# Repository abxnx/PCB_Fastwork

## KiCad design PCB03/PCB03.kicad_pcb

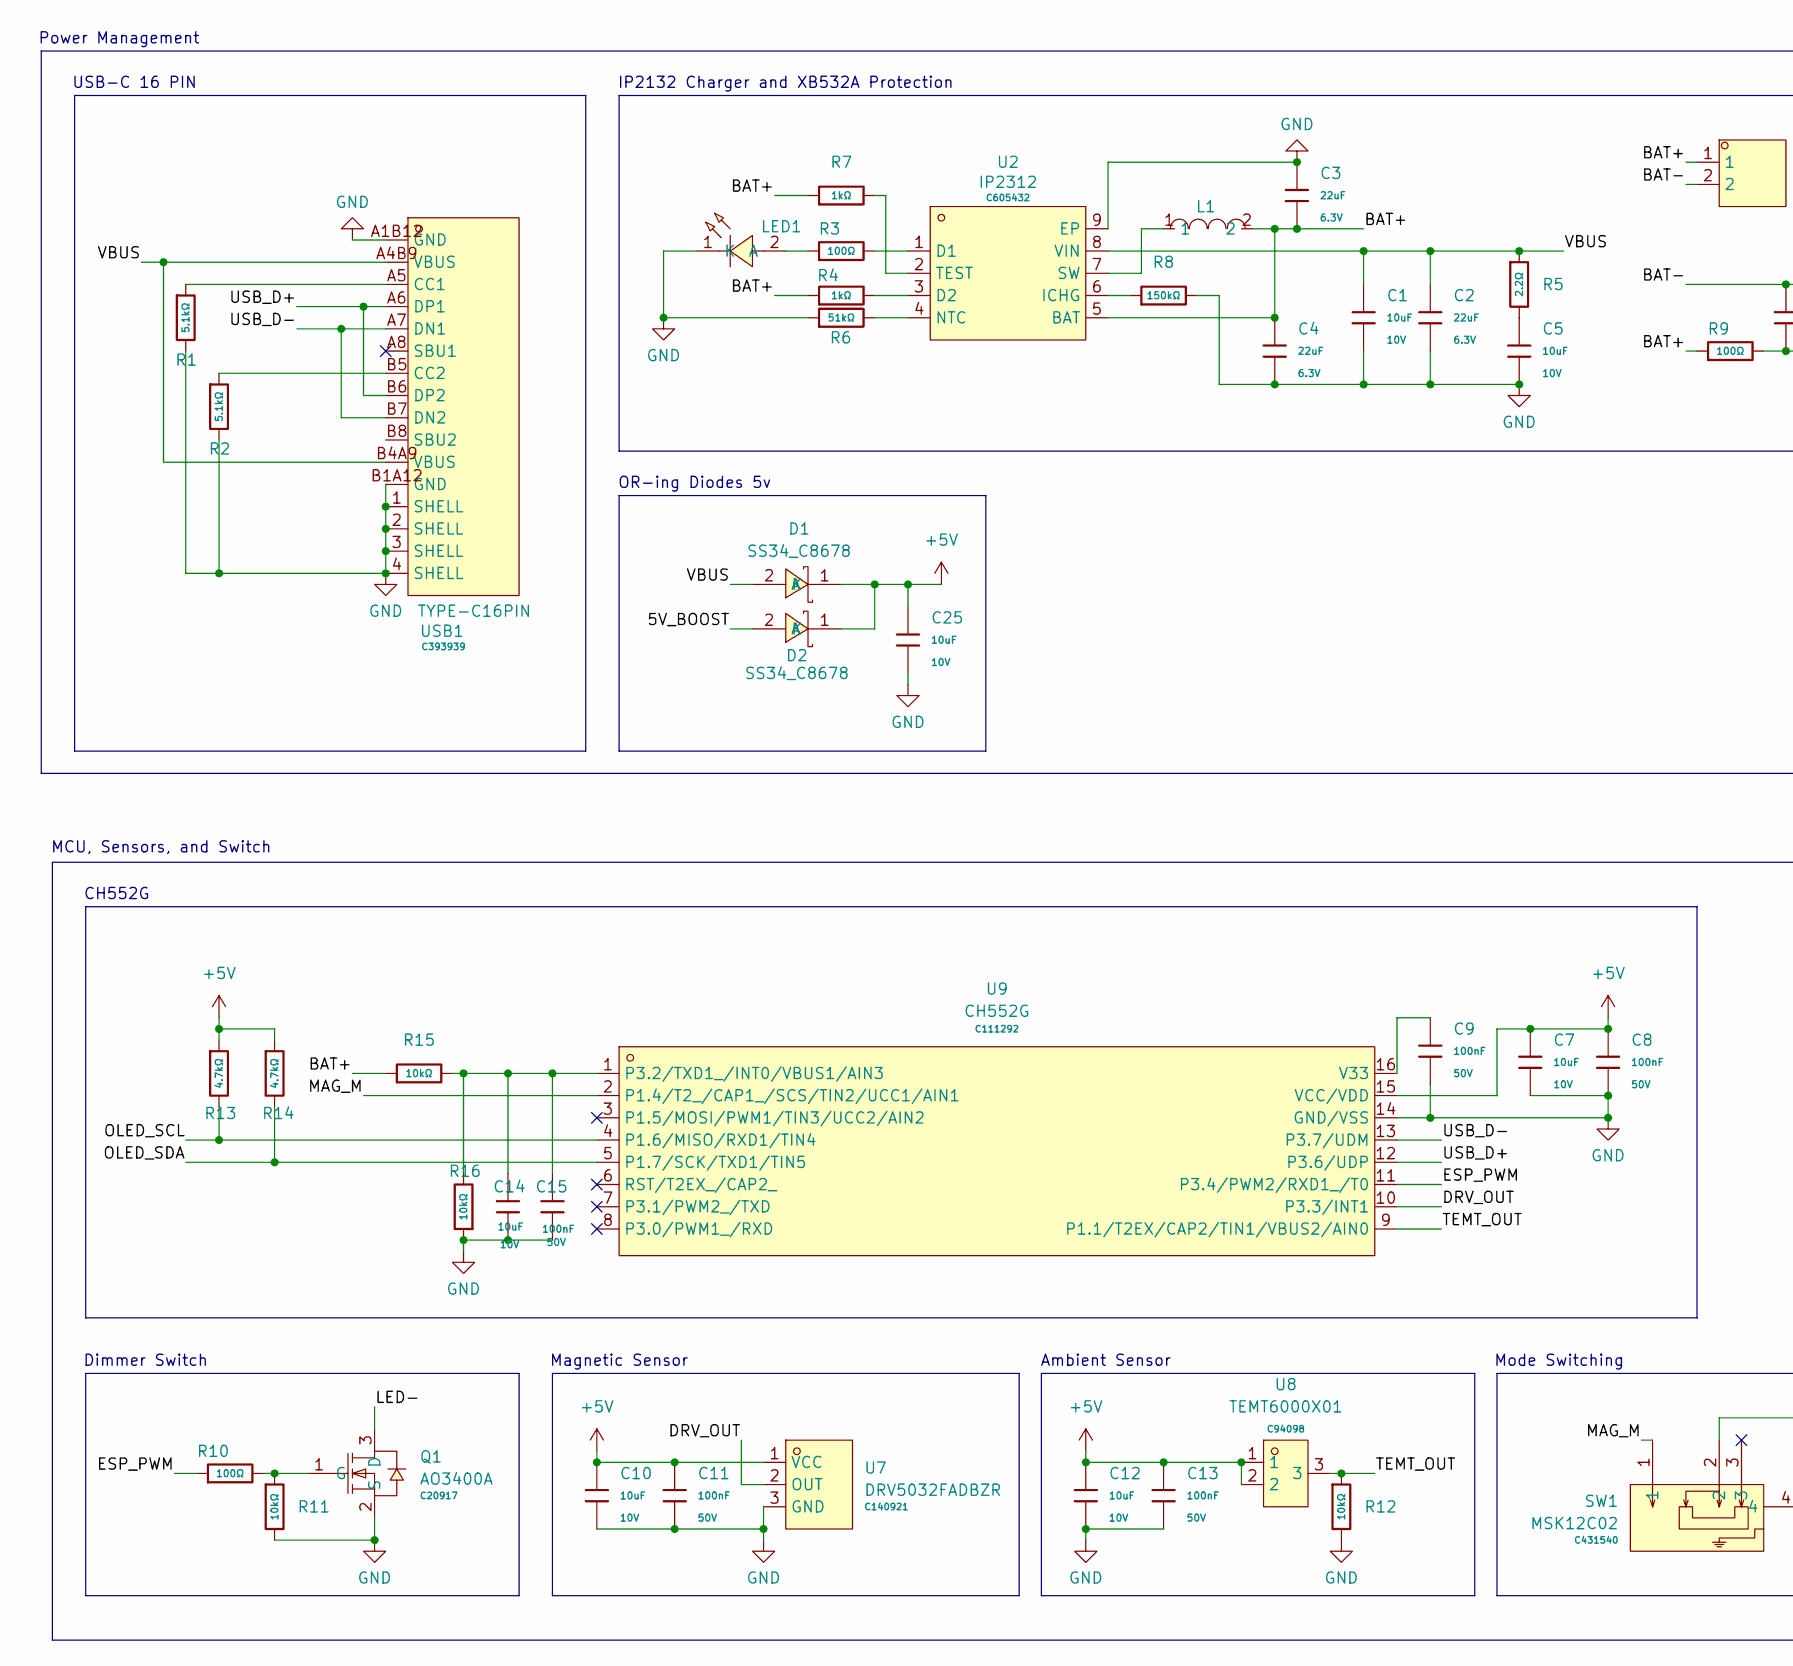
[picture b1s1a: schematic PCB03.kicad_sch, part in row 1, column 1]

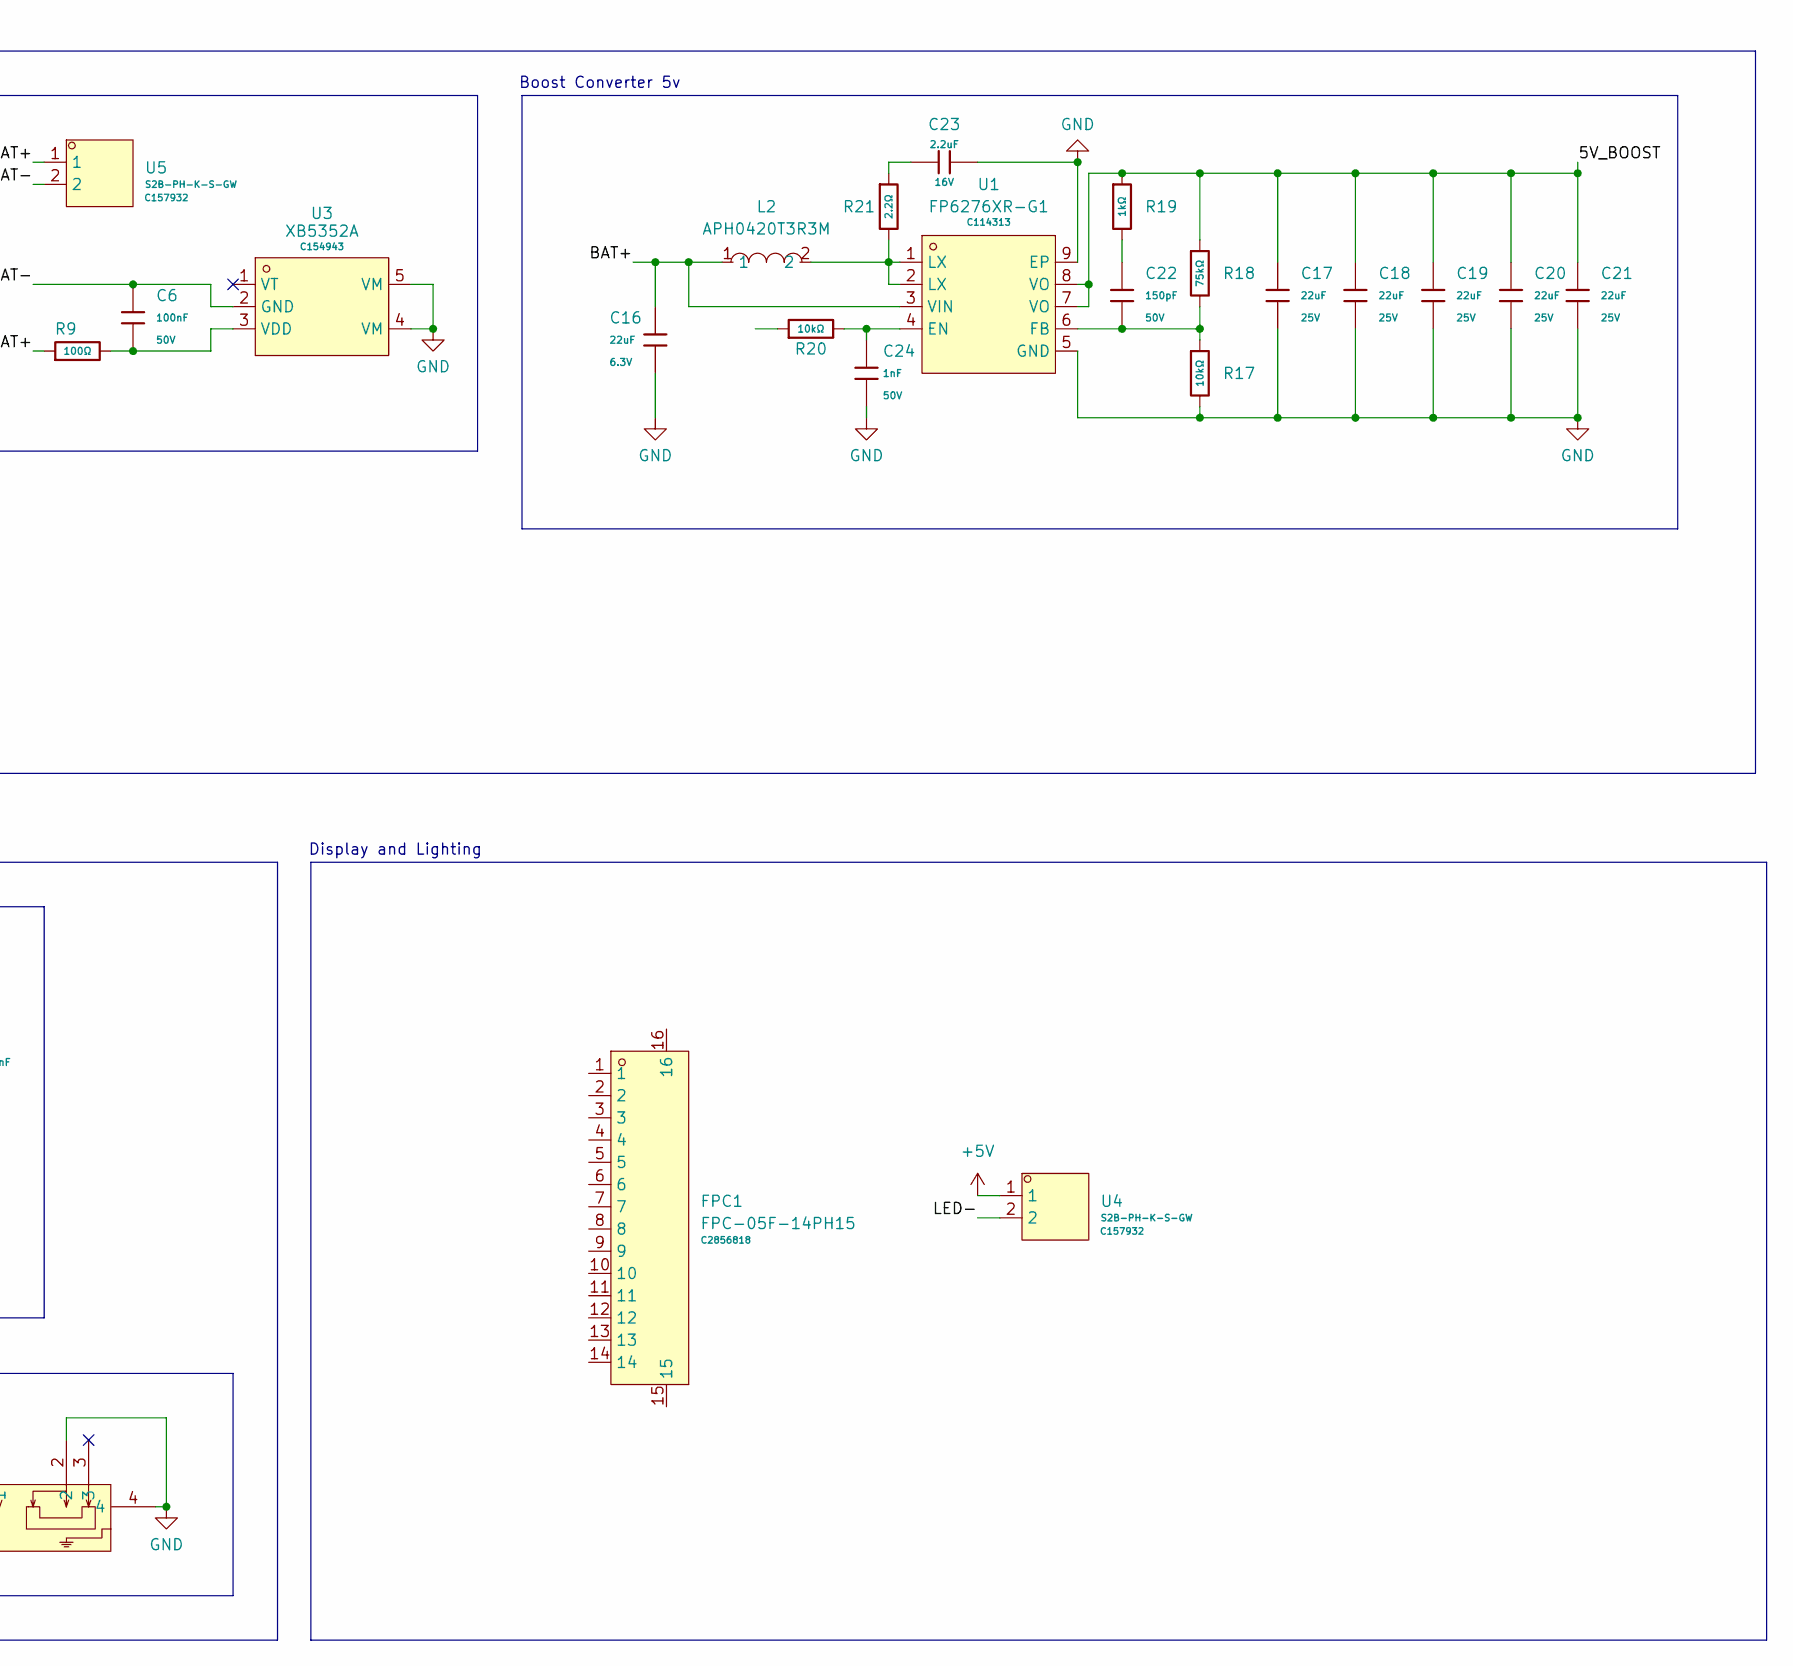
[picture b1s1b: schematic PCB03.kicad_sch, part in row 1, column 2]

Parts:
C1, C5, C7, C10, C12, C14, C25: 10uF; C_0603; Voltage Rated 10V; Tolerance ±10%; Part CL10A106KP8NNNC; LCSC C19702
C2, C3, C4, C16: 22uF; C_0603; Voltage Rated 6.3V; Tolerance ±20%; Part CL10A226MQ8NRNC; LCSC C59461
C6, C8, C9, C11, C13, C15: 100nF; C_0603; Voltage Rated 50V; Tolerance ±10%; Part CC0603KRX7R9BB104; LCSC C14663
C17, C18, C19, C20, C21: 22uF; C_0805; Voltage Rated 25V; Tolerance ±20%; Part CL21A226MAQNNNE; LCSC C45783
C22: 150pF; C_0603; Voltage Rated 50V; Tolerance ±10%; Part 0603B151K500NT; LCSC C1594
C23: 2.2uF; C_0603; Voltage Rated 16V; Tolerance ±10%; Part CL10A225KO8NNNC; LCSC C23630
C24: 1nF; C_0603; Voltage Rated 50V; Tolerance ±10%; Part CL10B102KB8NNNC; LCSC C1588
D1, D2: SS34_C8678; SMA_L4.3-W2.6-LS5.2-RD; MPN SS34; LCSC Part C8678
FPC1: FPC-05F-14PH15; FPC-SMD_14P-P0.50_XUNPU_FPC-05F-14PH15; MPN FPC-05F-14PH15; LCSC Part C2856818
L1: DFE252012F-1R0M=P2; L2520; MPN DFE252012F-1R0M=P2; LCSC Part C435392
L2: APH0420T3R3M; IND-SMD_L4.4-W4.2; MPN APH0420T3R3M; LCSC Part C5349667
LED1: XL-1608SURC-06; LED0603-RD_RED; MPN XL-1608SURC-06; LCSC Part C965799
Q1: AO3400A; SOT-23-3_L2.9-W1.3-P1.90-LS2.4-BR; MPN AO3400A; LCSC Part C20917
R1, R2: 5.1kΩ; R_0603; Overload Voltage (Max) 75V; Tolerance ±1%; Part 0603WAF5101T5E; LCSC C23186
R3, R9, R10: 100Ω; R_0603; Overload Voltage (Max) 75V; Tolerance ±1%; Part 0603WAF1000T5E; LCSC C22775
R4, R7, R19: 1kΩ; R_0603; Overload Voltage (Max) 75V; Tolerance ±1%; Part 0603WAF1001T5E; LCSC C21190
R5, R21: 2.2Ω; R_0603; Overload Voltage (Max) 75V; Tolerance ±1%; Part 0603WAF220KT5E; LCSC C22939
R6: 51kΩ; R_0603; Overload Voltage (Max) 75V; Tolerance ±1%; Part 0603WAF5102T5E; LCSC C23196
R8: 150kΩ; R_0603; Overload Voltage (Max) 75V; Tolerance ±1%; Part 0603WAF1503T5E; LCSC C22807
R11, R12, R15, R16, R17, R20: 10kΩ; R_0603; Overload Voltage (Max) 75V; Tolerance ±1%; Part 0603WAF1002T5E; LCSC C25804
R13, R14: 4.7kΩ; R_0603; Overload Voltage (Max) 75V; Tolerance ±1%; Part 0603WAF4701T5E; LCSC C23162
R18: 75kΩ; R_0603; Overload Voltage (Max) 75V; Tolerance ±1%; Part 0603WAF7502T5E; LCSC C23242
SW1: MSK12C02; SW-TH_MSK12C02; MPN MSK12C02; LCSC Part C431540
U1: FP6276XR-G1; SOP-8_L4.9-W3.9-P1.27-LS6.0-BL-EP; MPN FP6276XR-G1; LCSC Part C114313
U2: IP2312; SOP-8_L4.9-W3.9-P1.27-LS6.0-BL-EP; MPN IP2312U_VSET; LCSC Part C605432
U3: XB5352A; SOT-23-5_L3.0-W1.7-P0.95-LS2.8-BR; MPN XB5352A; LCSC Part C154943
U4, U5: S2B-PH-K-S-GW; CONN-TH_S2B-PH-K-S-GW; MPN S2B-PH-K-S-GW; LCSC Part C157932
U7: DRV5032FADBZR; SOT-23-3_L2.9-W1.3-P0.95-LS2.4-BR; MPN DRV5032FADBZR; LCSC Part C140921
U8: TEMT6000X01; SENSORS-SMD_TEMT6000X01; MPN TEMT6000X01; LCSC Part C94098
U9: CH552G; SOP-16_L10.0-W3.9-P1.27-LS6.0-BL; MPN CH552G; LCSC Part C111292
USB1: TYPE-C16PIN; USB-C-SMD_TYPE-C16PIN; MPN TYPE-C16PIN; LCSC Part C393939

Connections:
+5V: C7.1, C8.1, C10.1, C11.1, C12.1, C13.1, C25.1, D1.1 (K), D2.1 (K), R13.1, R14.1, U4.1, U7.1 (VCC), U8.1, U8.2, U9.15 (VCC/VDD)
/5V_BOOST: C17.1, C18.1, C19.1, C20.1, C21.1, D2.2 (A), R18.1, R19.1, U1.7 (VO), U1.8 (VO)
/BAT+: C3.2, C4.1, C16.1, L1.2, L2.1, R4.1, R7.1, R9.1, R15.1, U1.3 (VIN), U2.5 (BAT), U5.1
/BAT-: C6.1, U3.2 (GND), U5.2
/DRV_OUT: U7.2 (OUT), U9.10 (P3.3/INT1)
/ESP_PWM: R10.1, U9.11 (P3.4/PWM2/RXD1_/T0)
/LED-: Q1.3 (D), U4.2
/MAG_M: SW1.1, U9.2 (P1.4/T2_/CAP1_/SCS/TIN2/UCC1/AIN1)
/OLED_SCL: R13.2, U9.4 (P1.6/MISO/RXD1/TIN4)
/OLED_SDA: R14.2, U9.5 (P1.7/SCK/TXD1/TIN5)
/TEMT_OUT: R12.1, U8.3, U9.9 (P1.1/T2EX/CAP2/TIN1/VBUS2/AIN0)
/USB_D+: U9.12 (P3.6/UDP), USB1.A6 (DP1), USB1.B6 (DP2)
/USB_D-: U9.13 (P3.7/UDM), USB1.A7 (DN1), USB1.B7 (DN2)
/VBUS: C1.1, C2.1, D1.2 (A), R5.1, U2.8 (VIN), USB1.A4B9 (VBUS), USB1.B4A9 (VBUS)
GND: C1.2, C2.2, C3.1, C4.2, C5.2, C7.2, C8.2, C9.2, C10.2, C11.2, C12.2, C13.2, C14.2, C15.2, C16.2, C17.2, C18.2, C19.2, C20.2, C21.2, C23.2, C24.2, C25.2, LED1.1 (K), Q1.2 (S), R1.2, R2.2, R6.1, R8.2, R11.2, R12.2, R16.1, R17.2, SW1.2, SW1.4, U1.5 (GND), U1.9 (EP), U2.9 (EP), U3.4 (VM), U3.5 (VM), U7.3 (GND), U9.14 (GND/VSS), USB1.1 (SHELL), USB1.2 (SHELL), USB1.3 (SHELL), USB1.4 (SHELL), USB1.A1B12 (GND), USB1.B1A12 (GND)
unnamed: C5.1, R5.2
unnamed: C22.1, R19.2
unnamed: C23.1, R21.1
unnamed: L2.2, R21.2, U1.1 (LX), U1.2 (LX)
unnamed: LED1.2 (A), R3.1
unnamed: Q1.1 (G), R10.2, R11.1
unnamed: C24.1, R20.2, U1.4 (EN)
unnamed: C22.2, R17.1, R18.2, U1.6 (FB)
unnamed: R3.2, U2.1 (D1)
unnamed: R4.2, U2.3 (D2)
unnamed: R8.1, U2.6 (ICHG)
unnamed: R6.2, U2.4 (NTC)
unnamed: L1.1, U2.7 (SW)
unnamed: R7.2, U2.2 (TEST)
unnamed: C6.2, R9.2, U3.3 (VDD)
unnamed: C14.1, C15.1, R15.2, R16.2, U9.1 (P3.2/TXD1_/INT0/VBUS1/AIN3)
unnamed: C9.1, U9.16 (V33)
unnamed: R1.1, USB1.A5 (CC1)
unnamed: R2.1, USB1.B5 (CC2)

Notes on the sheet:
Display and Lighting
Magnetic Sensor
USB-C 16 PIN
CH552G
Dimmer Switch
Power Management
IP2132 Charger and XB532A Protection
OR-ing Diodes 5v
MCU, Sensors, and Switch
Mode Switching
Ambient Sensor
Boost Converter 5v

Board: 2 copper layers, 63 parts (0 on the bottom side), 34 nets, no tracks yet.

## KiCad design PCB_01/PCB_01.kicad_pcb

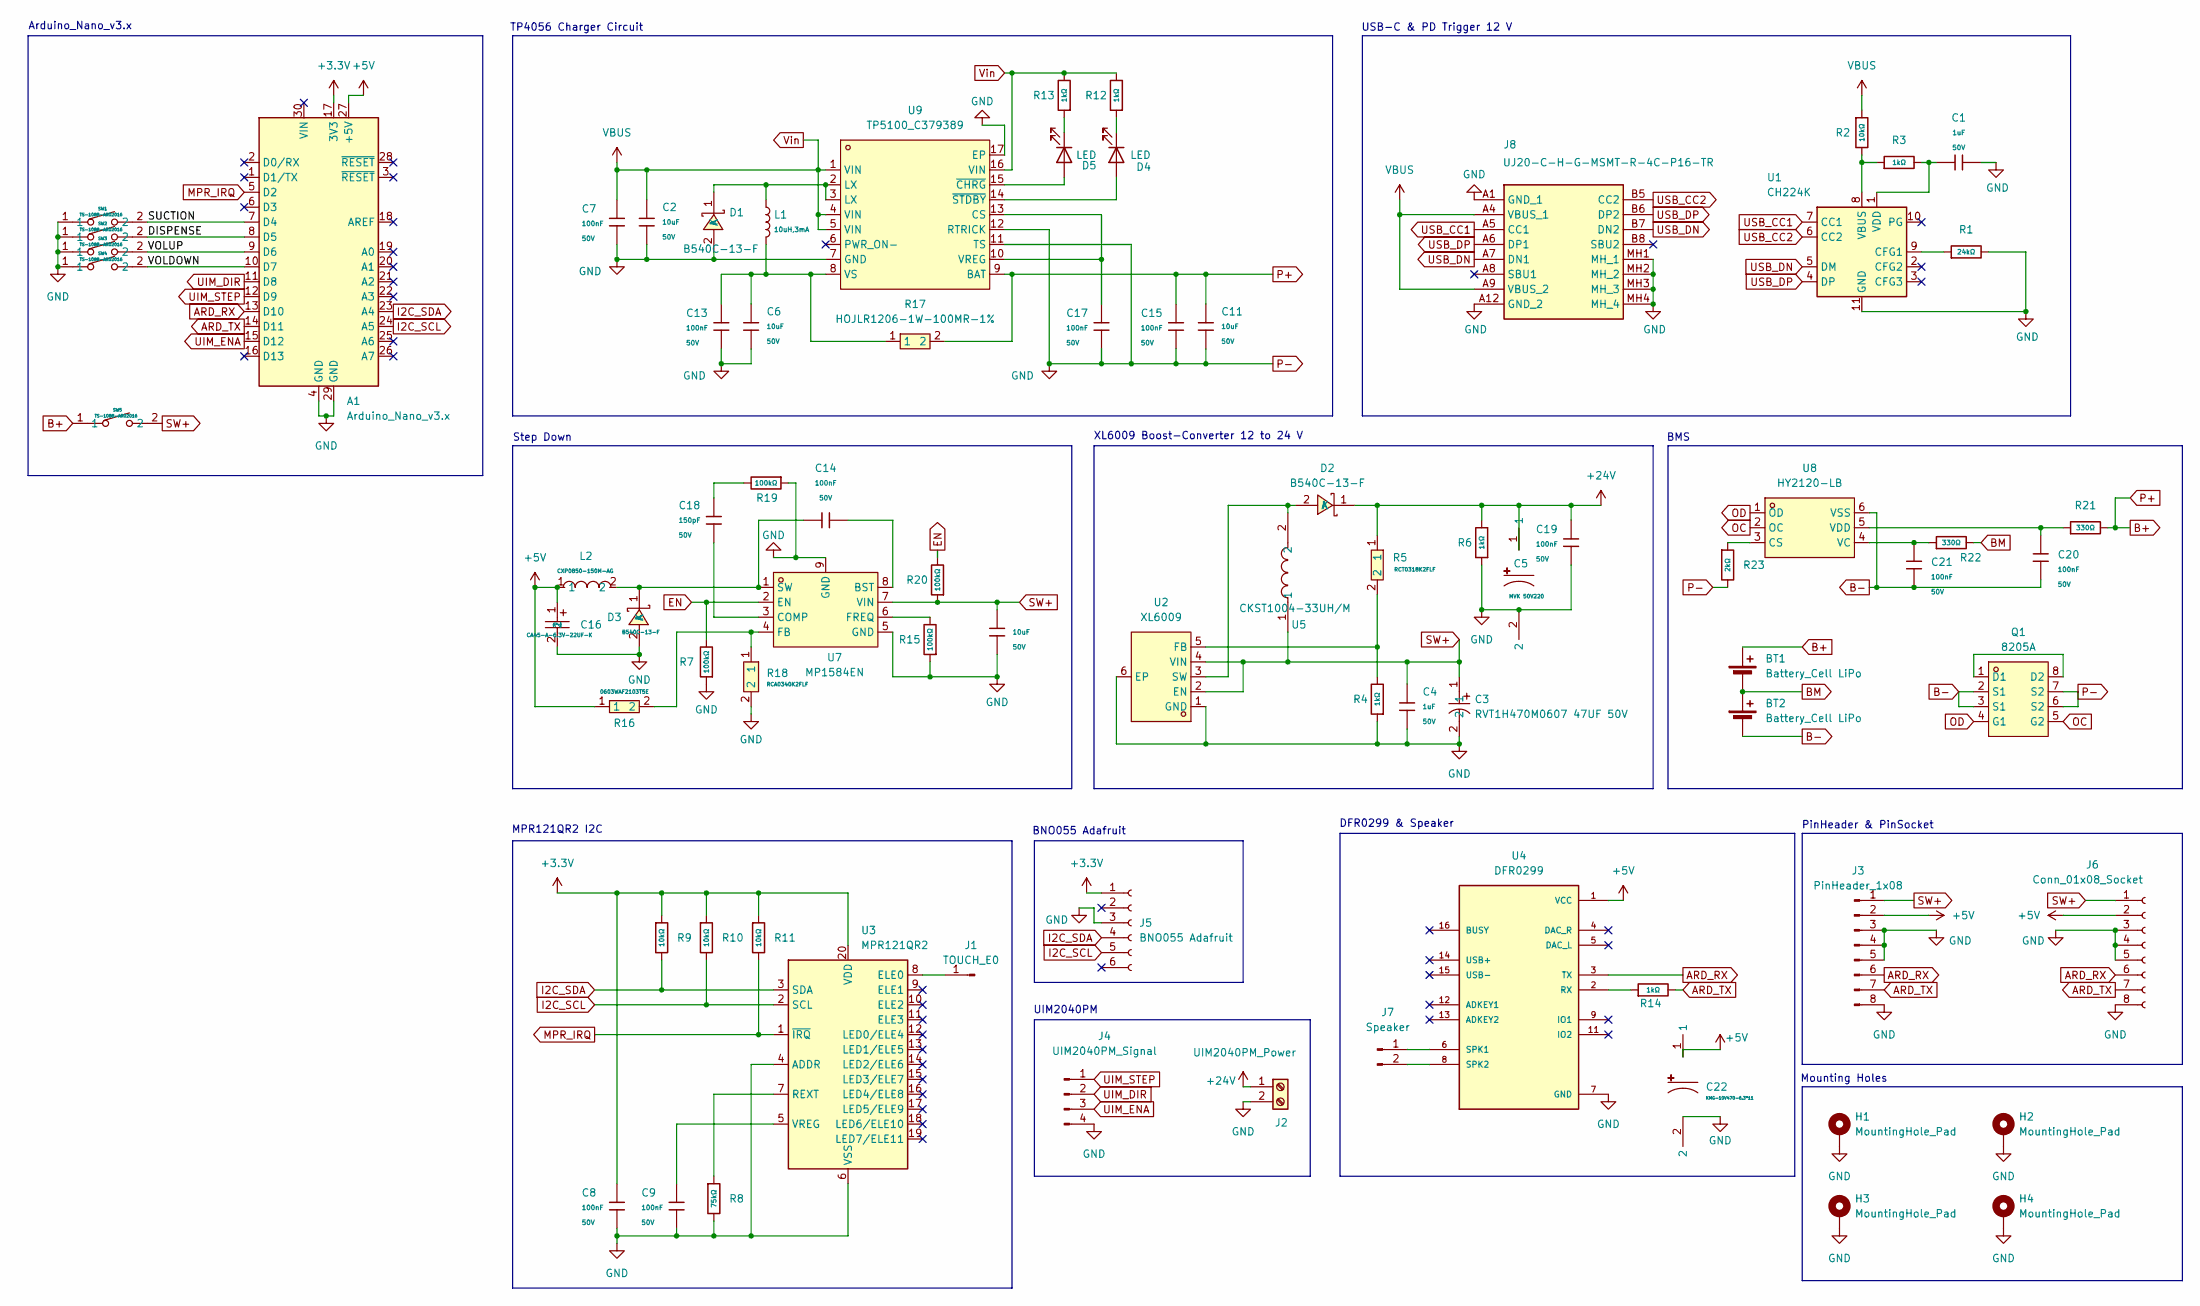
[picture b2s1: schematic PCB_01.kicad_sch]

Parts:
A1: Arduino_Nano_v3.x; Arduino_Nano
BT1, BT2: Battery_Cell LiPo; JST_PH_S2B-PH-K_1x02_P2.00mm_Horizontal
C1, C4: 1uF; C_0603; Voltage Rated 50V; Tolerance ±10%; Part CL10A105KB8NNNC; LCSC C15849
C2, C6, C11, C12: 10uF; C_1206; Voltage Rated 50V; Tolerance ±10%; Part CL31A106KBHNNNE; LCSC C13585
C3: RVT1H470M0607 47UF 50V; CAP-SMD_BD6.3-L6.6-W6.6-LS7.2-FD; MPN RVT1H470M0607 47UF 50V; LCSC Part C970679
C5: MVK 50V220; CAP-SMD_BD10.0-L10.3-W10.3-FD; MPN MVK50V220M10*10 10TP; LCSC Part C165588
C7, C8, C9, C13, C14, C15, C17, C19, C20, C21: 100nF; C_0603; Voltage Rated 50V; Tolerance ±10%; Part CC0603KRX7R9BB104; LCSC C14663
C16: CA45-A-6.3V-22UF-K; CASE-A_3216; MPN CA45-A-6.3V-22uF-K; LCSC Part C129288
C18: 150pF; C_0603; Voltage Rated 50V; Tolerance ±10%; Part 0603B151K500NT; LCSC C1594
C22: KMG-10V470-6.3*11; CAP-TH_BD6.3-P2.50-D1.0-FD; MPN KMG 10V470 6.3*11; LCSC Part C349987
D1, D2, D3: B540C-13-F; SMC_L7.1-W6.2-LS8.1-RD; MPN B540C-13-F; LCSC Part C72264
D4, D5: LED; LED_0805_2012Metric
H1, H2, H3, H4: MountingHole_Pad; MountingHole_2.2mm_M2_DIN965_Pad
J1: TOUCH_E0; SolderWire-0.1sqmm_1x01_D0.4mm_OD1mm
J2: UIM2040PM_Power; TerminalBlock_Phoenix_MKDS-1,5-2_1x02_P5.00mm_Horizontal
J3: PinHeader_1x08; PinHeader_1x08_P1.00mm_Vertical
J4: UIM2040PM_Signal; PinHeader_1x04_P1.00mm_Vertical
J5: BNO055 Adafruit; PinSocket_1x06_P2.54mm_Vertical
J6: Conn_01x08_Socket; PinSocket_1x08_P1.00mm_Vertical
J7: Speaker; JST_PH_S2B-PH-K_1x02_P2.00mm_Horizontal
J8: UJ20-C-H-G-MSMT-R-4C-P16-TR; UJ20CHGMSMTR4CP16TR; Manufacturer_Part_Number UJ20-C-H-G-MSMT-R-4C-P16-TR
L1: 10uH,3mA; L_0603; Tolerance ±10%; Part SDFL1608S100KTF; LCSC C1035
L2: CXP0850-150M-AG; IND-SMD_L8.5-W8.0_PCC-M0854M; MPN CXP0850-150M-AG(15UH); LCSC Part C7461738
Q1: 8205A; TSSOP-8_L4.4-W3.0-P0.65-LS6.4-BL; MPN 8205A; LCSC Part C181100
R1: 24kΩ; R_0603; Overload Voltage (Max) 75V; Tolerance ±1%; Part 0603WAF2402T5E; LCSC C23352
R2, R9, R10, R11: 10kΩ; R_0603; Overload Voltage (Max) 75V; Tolerance ±1%; Part 0603WAF1002T5E; LCSC C25804
R3, R4, R6, R12, R13, R14: 1kΩ; R_0603; Overload Voltage (Max) 75V; Tolerance ±1%; Part 0603WAF1001T5E; LCSC C21190
R5: RCT0318K2FLF; R0603; MPN RCT0318K2FLF; LCSC Part C178097
R7, R15, R19, R20: 100kΩ; R_0603; Overload Voltage (Max) 75V; Tolerance ±1%; Part 0603WAF1003T5E; LCSC C25803
R8: 75kΩ; R_0603; Overload Voltage (Max) 75V; Tolerance ±1%; Part 0603WAF7502T5E; LCSC C23242
R16: 0603WAF2103T5E; R0603; MPN 0603WAF2103T5E; LCSC Part C22952
R17: HOJLR1206-1W-100MR-1%; RES-SMD_L3.2-W1.6_SY1206; MPN HoJLR1206-1W-100mR-1%; LCSC Part C2903496
R18: RCA0340K2FLF; R0603; MPN RCA0340K2FLF; LCSC Part C22369806
R21, R22: 330Ω; R_0603; Overload Voltage (Max) 75V; Tolerance ±1%; Part 0603WAF3300T5E; LCSC C23138
R23: 2kΩ; R_0603; Overload Voltage (Max) 75V; Tolerance ±1%; Part 0603WAF2001T5E; LCSC C22975
SW1, SW2, SW3, SW4, SW5: TS-1088-AR02016; SW-SMD_L3.9-W3.0-P4.45; MPN TS-1088-AR02016; LCSC Part C720477
U1: CH224K; SSOP-10-1EP_3.9x4.9mm_P1mm_EP2.1x3.3mm
U2: XL6009; TO-263-5_L10.2-W8.6-P1.70-LS14.4-TL; MPN XL6009; LCSC Part C15831
U3: MPR121QR2; UQFN-20_3x3mm_P0.4mm
U4: DFR0299; MODULE_DFR0299
U5: CKST1004-33UH/M; IND-SMD_L11.6-W10.1; MPN CKST1004-33uH/M; LCSC Part C3002689
U7: MP1584EN; SOIC-8_L4.9-W3.9-P1.27-LS6.0-BL-EP3.3; MPN MP1584EN; LCSC Part C454188
U8: HY2120-LB; SOT-23-6_L2.9-W1.6-P0.95-LS2.8-BR; MPN HY2120-LB; LCSC Part C168778
U9: TP5100_C379389; TQFN-16_L4.0-W4.0-P0.65-BL-EP; MPN TP5100; LCSC Part C379389

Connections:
+3.3V: A1.17 (3V3), C8.1, J5.1, R9.1, R10.1, R11.1, U3.20 (VDD)
+5V: A1.27 (+5V), C16.1, C22.1, J3.2, J6.2, L2.1, R16.1, U4.1 (VCC)
+24V: C5.1, C19.1, D2.1 (K), J2.1, R5.1, R6.2
/DISPENSE: A1.8 (D5), SW2.2
/SUCTION: A1.7 (D4), SW1.2
/VOLDOWN: A1.10 (D7), SW4.2
/VOLUP: A1.9 (D6), SW3.2
ARD_RX: A1.13 (D10), J3.6, J6.6, U4.3 (TX)
ARD_TX: A1.14 (D11), J3.7, J6.7, R14.2
B+: BT1.1 (+), C11.1, C15.1, R17.2, R21.2, SW5.1, U9.9 (BAT)
B-: BT2.2 (-), C20.2, C21.2, Q1.2 (S1), Q1.3 (S1), U8.6 (VSS)
BM: BT1.2 (-), BT2.1 (+), R22.2
EN: R7.2, R20.2, U7.2 (EN)
I2C_SCL: A1.24 (A5), J5.5, R10.2, U3.2 (SCL)
I2C_SDA: A1.23 (A4), J5.4, R9.2, U3.3 (SDA)
MPR_IRQ: A1.5 (D2), R11.2, U3.1 (~IRQ)
unnamed: C18.1, R19.2
unnamed: D1.1 (K), L1.1, U9.2 (LX), U9.3 (LX)
unnamed: D2.2 (A), U2.3 (SW), U5.2
unnamed: C14.1, D3.1 (K), L2.2, U7.1 (SW)
unnamed: D4.2 (A), U9.14 (~STDBY)
unnamed: D4.1 (K), R12.1
unnamed: D5.2 (A), U9.15 (~CHRG)
unnamed: D5.1 (K), R13.1
unnamed: J1.1, U3.8 (ELE0)
unnamed: J7.1, U4.6 (SPK1)
unnamed: J7.2, U4.8 (SPK2)
unnamed: Q1.1 (D1), Q1.8 (D2)
unnamed: R1.1, U1.9 (CFG1)
unnamed: R2.2, R3.1, U1.8 (VBUS)
unnamed: C1.2, R3.2, U1.1 (VDD)
unnamed: R4.2, R5.2, U2.5 (FB)
unnamed: R8.1, U3.7 (REXT)
unnamed: C9.1, U3.5 (VREG)
unnamed: R14.1, U4.2 (RX)
unnamed: C14.2, U7.8 (BST)
unnamed: C18.2, U7.3 (COMP)
unnamed: R16.2, R18.1, U7.4 (FB)
unnamed: R15.2, U7.6 (FREQ)
unnamed: R23.1, U8.3 (CS)
unnamed: C21.1, R22.1, U8.4 (VC)
unnamed: C20.1, R21.1, U8.5 (VDD)
unnamed: C17.1, U9.10 (VREG), U9.13 (CS)
unnamed: C6.1, C13.1, L1.2, R17.1, U9.8 (VS)
OC: Q1.5 (G2), U8.2 (OC)
OD: Q1.4 (G1), U8.1 (OD)
P-: A1.4 (GND), A1.29 (GND), C1.1, C2.2, C3.2, C4.2, C5.2, C6.2, C7.2, C8.2, C9.2, C11.2, C12.2, C13.2, C15.2, C16.2, C17.2, C19.2, C22.2, D1.2 (A), D3.2 (A), H1.1, H2.1, H3.1, H4.1, J2.2, J3.3, J3.4, J3.5, J3.8, J4.4, J5.3, J6.3, J6.4, J6.5, J6.8, J8.A1 (GND_1), J8.A12 (GND_2), J8.MH1 (MH_1), J8.MH2 (MH_2), J8.MH3 (MH_3), J8.MH4 (MH_4), Q1.6 (S2), Q1.7 (S2), R1.2, R4.1, R6.1, R7.1, R8.2, R15.1, R18.2, R19.1, R23.2, SW1.1, SW2.1, SW3.1, SW4.1, U1.11 (GND), U2.1 (GND), U2.6 (EP), U3.4 (ADDR), U3.6 (VSS), U4.7 (GND), U4.10 (GND), U7.5 (GND), U7.9 (GND), U9.7 (GND), U9.11 (TS), U9.12 (RTRICK), U9.17 (EP)
SW+: C3.1, C4.1, C12.1, J3.1, J6.1, R20.1, SW5.2, U2.2 (EN), U2.4 (VIN), U5.1, U7.7 (VIN)
UIM_DIR: A1.11 (D8), J4.2
UIM_ENA: A1.15 (D12), J4.3
UIM_STEP: A1.12 (D9), J4.1
USB_CC1: J8.A5 (CC1), U1.7 (CC1)
USB_CC2: J8.B5 (CC2), U1.6 (CC2)
USB_DN: J8.A7 (DN1), J8.B7 (DN2), U1.5 (DM)
USB_DP: J8.A6 (DP1), J8.B6 (DP2), U1.4 (DP)
Vin: C2.1, C7.1, J8.A4 (VBUS_1), J8.A9 (VBUS_2), R2.1, R12.2, R13.2, U9.1 (VIN), U9.4 (VIN), U9.5 (VIN), U9.16 (VIN)

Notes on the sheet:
UIM2040PM
TP4056 Charger Circuit
Step Down
DFR0299 & Speaker
Mounting Holes
Arduino_Nano_v3.x
XL6009 Boost-Converter 12 to 24 V
MPR121QR2 I2C
USB-C & PD Trigger 12 V
BMS
PinHeader & PinSocket
BNO055 Adafruit

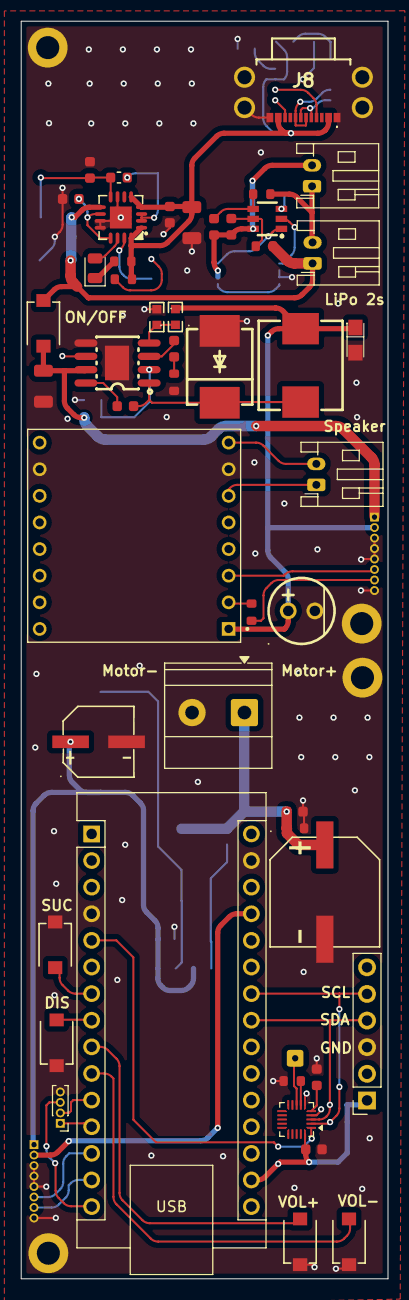
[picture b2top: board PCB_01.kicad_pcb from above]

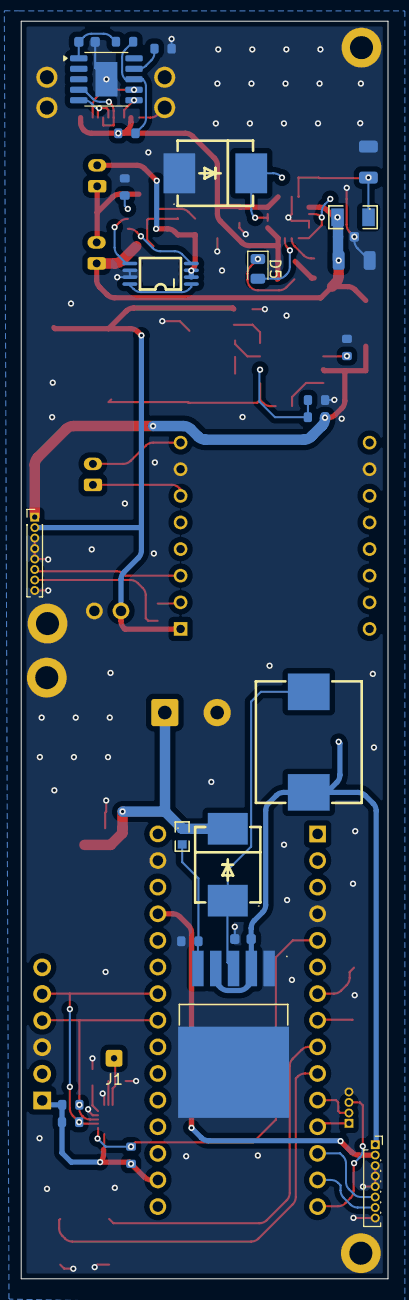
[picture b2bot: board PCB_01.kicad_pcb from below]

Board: 2 copper layers, 35.0 x 120.0 mm, 80 parts (28 on the bottom side), 56 nets.

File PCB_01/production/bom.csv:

Designator,Footprint,Quantity,Value,LCSC Part #
A1,Arduino_Nano,1,Arduino_Nano_v3.x,
"BT1, BT2",JST_PH_S2B-PH-K_1x02_P2.00mm_Horizontal,2,Battery_Cell LiPo,
"C1, C4",C_0603,2,1uF,C15849
"C11, C12, C2, C6",C_1206,4,10uF,C13585
"C13, C14, C15, C17, C19, C20, C21, C7, C8, C9",C_0603,10,100nF,C14663
C16,CASE-A_3216,1,CA45-A-6.3V-22UF-K,C129288
C18,C_0603,1,150pF,C1594
C22,CAP-TH_BD6.3-P2.50-D1.0-FD,1,KMG-10V470-6.3*11,C349987
C3,CAP-SMD_BD6.3-L6.6-W6.6-LS7.2-FD,1,RVT1H470M0607 47UF 50V,C970679
C5,CAP-SMD_BD10.0-L10.3-W10.3-FD,1,MVK 50V220,C165588
"D1, D2, D3",SMC_L7.1-W6.2-LS8.1-RD,3,B540C-13-F,C72264
"D4, D5",0805,2,LED,
J1,SolderWire-0.1sqmm_1x01_D0.4mm_OD1mm,1,TOUCH_E0,
J2,"TerminalBlock_Phoenix_MKDS-1,5-2_1x02_P5.00mm_Horizontal",1,UIM2040PM_Power,
J3,PinHeader_1x08_P1.00mm_Vertical,1,PinHeader_1x08,
J4,PinHeader_1x04_P1.00mm_Vertical,1,UIM2040PM_Signal,
J5,PinSocket_1x06_P2.54mm_Vertical,1,BNO055 Adafruit,
J6,PinSocket_1x08_P1.00mm_Vertical,1,Conn_01x08_Socket,
J7,JST_PH_S2B-PH-K_1x02_P2.00mm_Horizontal,1,Speaker,
J8,UJ20CHGMSMTR4CP16TR,1,UJ20-C-H-G-MSMT-R-4C-P16-TR,
L1,L_0603,1,"10uH,3mA",C1035
L2,IND-SMD_L8.5-W8.0_PCC-M0854M,1,CXP0850-150M-AG,C7461738
Q1,TSSOP-8_L4.4-W3.0-P0.65-LS6.4-BL,1,8205A,C181100
R1,R_0603,1,24kΩ,C23352
"R10, R11, R2, R9",R_0603,4,10kΩ,C25804
"R12, R13, R14, R3, R4, R6",R_0603,6,1kΩ,C21190
"R15, R19, R20, R7",R_0603,4,100kΩ,C25803
R16,R0603,1,0603WAF2103T5E,C22952
R17,RES-SMD_L3.2-W1.6_SY1206,1,HOJLR1206-1W-100MR-1%,C2903496
R18,R0603,1,RCA0340K2FLF,C22369806
"R21, R22",R_0603,2,330Ω,C23138
R23,R_0603,1,2kΩ,C22975
R5,R0603,1,RCT0318K2FLF,C178097
R8,R_0603,1,75kΩ,C23242
"SW1, SW2, SW3, SW4, SW5",SW-SMD_L3.9-W3.0-P4.45,5,TS-1088-AR02016,C720477
U1,SSOP-10-1EP_3.9x4.9mm_P1mm_EP2.1x3.3mm,1,CH224K,
U2,TO-263-5_L10.2-W8.6-P1.70-LS14.4-TL,1,XL6009,C15831
U3,UQFN-20_3x3mm_P0.4mm,1,MPR121QR2,
U4,MODULE_DFR0299,1,DFR0299,
U5,IND-SMD_L11.6-W10.1,1,CKST1004-33UH/M,C3002689
U7,SOIC-8_L4.9-W3.9-P1.27-LS6.0-BL-EP3.3,1,MP1584EN,C454188
U8,SOT-23-6_L2.9-W1.6-P0.95-LS2.8-BR,1,HY2120-LB,C168778
U9,TQFN-16_L4.0-W4.0-P0.65-BL-EP,1,TP5100_C379389,C379389

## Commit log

2026-05-11 chore: repo setup
2026-06-01 Update KiCad PCB layout and schematic, add Molex connector footprints and STEP models, and generate production outputs (BOM, interactive BOM, positions, and fabrication zip files)
2026-06-17 Add PCB03 folder
2026-06-17 Remove all folders except PCB03 on this branch
